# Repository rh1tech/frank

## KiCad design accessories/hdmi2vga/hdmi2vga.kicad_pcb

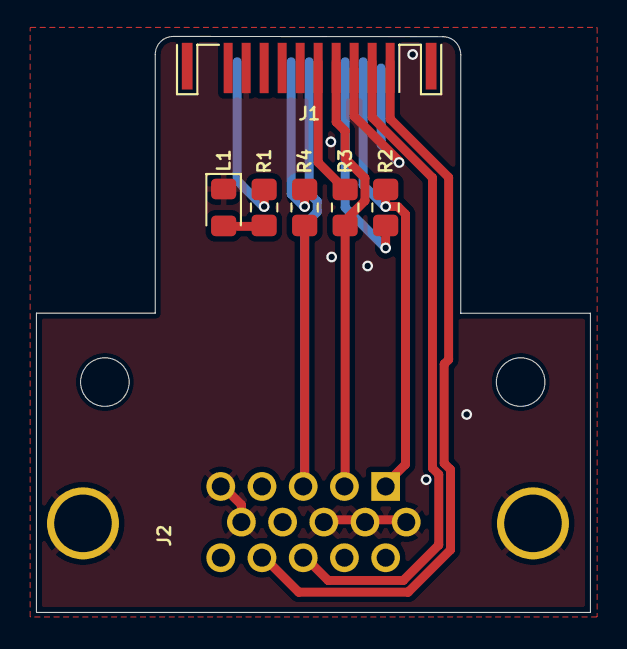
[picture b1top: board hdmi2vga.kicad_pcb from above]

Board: 2 copper layers, 30.8 x 32.0 mm, 9 parts (0 on the bottom side), 11 nets.

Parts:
H1, H2: MountingHole; Mounting Hole (2.7mm)
J1: HDMI; HDMI (male)
J2: VGA; D-SUB (15 pin, female)
L1: HDMI LED; LED (0805)
R1: 1K; Resistor (0805)
R2, R3, R4: 820R; Resistor (0805)

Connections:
/CLKN_VGA_B: J1.12 (CLKN), R4.1
/CLKP_VGA_BH: J1.10 (CLKP), J2.3, R4.2
/D0N_VGA_G: J1.9 (D0N), R3.1
/D0P_VGA_GH: J1.7 (D0P), J2.2, R3.2
/D1N_VGA_R: J1.6 (D1N), R2.1
/D1P_VGA_RH: J1.4 (D1P), J2.1, R2.2
/D2N_VGA_HS: J1.3 (D2N), J2.13
/D2P_VGA_VS: J1.1 (D2P), J2.14
GND: J1.2 (G_D2), J1.5 (G_D1), J1.8 (G_D0), J1.11 (G_CLK), J1.17 (G_DDC/CEC), J2.0, J2.5, J2.6, J2.7, J2.8, J2.10, L1.1 (K)
unnamed: J1.18 (+5V), R1.1
unnamed: L1.2 (A), R1.2

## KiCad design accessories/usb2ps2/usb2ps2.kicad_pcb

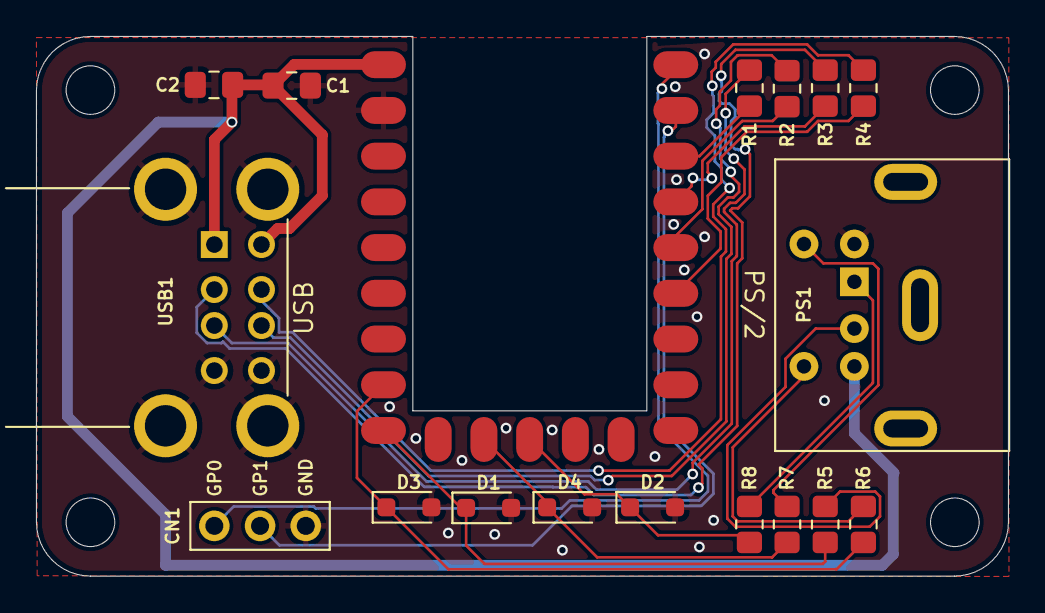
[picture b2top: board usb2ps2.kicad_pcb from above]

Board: 2 copper layers, 54.0 x 30.0 mm, 22 parts (0 on the bottom side), 20 nets.

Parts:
C1, C2: 10u; Capacitor (0805)
CN1: UART; Pin Header (1x03)
D1, D2, D3, D4: 3V3; Diode (SOD-323)
H1, H2, H3, H4: MountingHole; Mounting Hole (2.7mm)
PS1: PS/2; MiniDIN (6 Pin, female)
R1, R2, R3, R4: 22R; Resistor (0805)
R5, R6, R7, R8: 100R; Resistor (0805)
RP1: RP 2040 Zero; Raspberry Pi Zero (on board)
USB1: USB_A_Stacked; USB Type A (stacked)

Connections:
/GPIO0: CN1.1, RP1.1 (0)
/GPIO1: CN1.2, RP1.2 (1)
/GPIO2: R1.1, RP1.3 (2)
/GPIO3: R3.1, RP1.4 (3)
/GPIO4: R2.1, RP1.5 (4)
/GPIO5: R4.1, RP1.6 (5)
/GPIO11: D2.1 (K), R8.2, RP1.12 (11)
/GPIO12: D4.1 (K), R7.2, RP1.13 (12)
/GPIO14: D1.1 (K), R5.2, RP1.15 (14)
/GPIO15: D3.1 (K), R6.2, RP1.16 (15)
/PS2 with Diodes/KB_CLK: PS1.5, R7.1
/PS2 with Diodes/KB_DATA: PS1.1, R8.1
/PS2 with Diodes/MS_CLK: PS1.6, R6.1
/PS2 with Diodes/MS_DATA: PS1.2, R5.1
GND: C1.2, C2.2, CN1.3, D1.2 (A), D2.2 (A), D3.2 (A), D4.2 (A), PS1.3, RP1.22 (GND), USB1.4 (GND1), USB1.8 (GND2), USB1.9 (Shield)
unnamed: R1.2, USB1.3 (D1+)
unnamed: R3.2, USB1.2 (D1-)
unnamed: R2.2, USB1.7 (D2+)
unnamed: R4.2, USB1.6 (D2-)
VBUS: C1.1, C2.1, PS1.4, RP1.23 (5V), USB1.1 (VBUS1), USB1.5 (VBUS2)

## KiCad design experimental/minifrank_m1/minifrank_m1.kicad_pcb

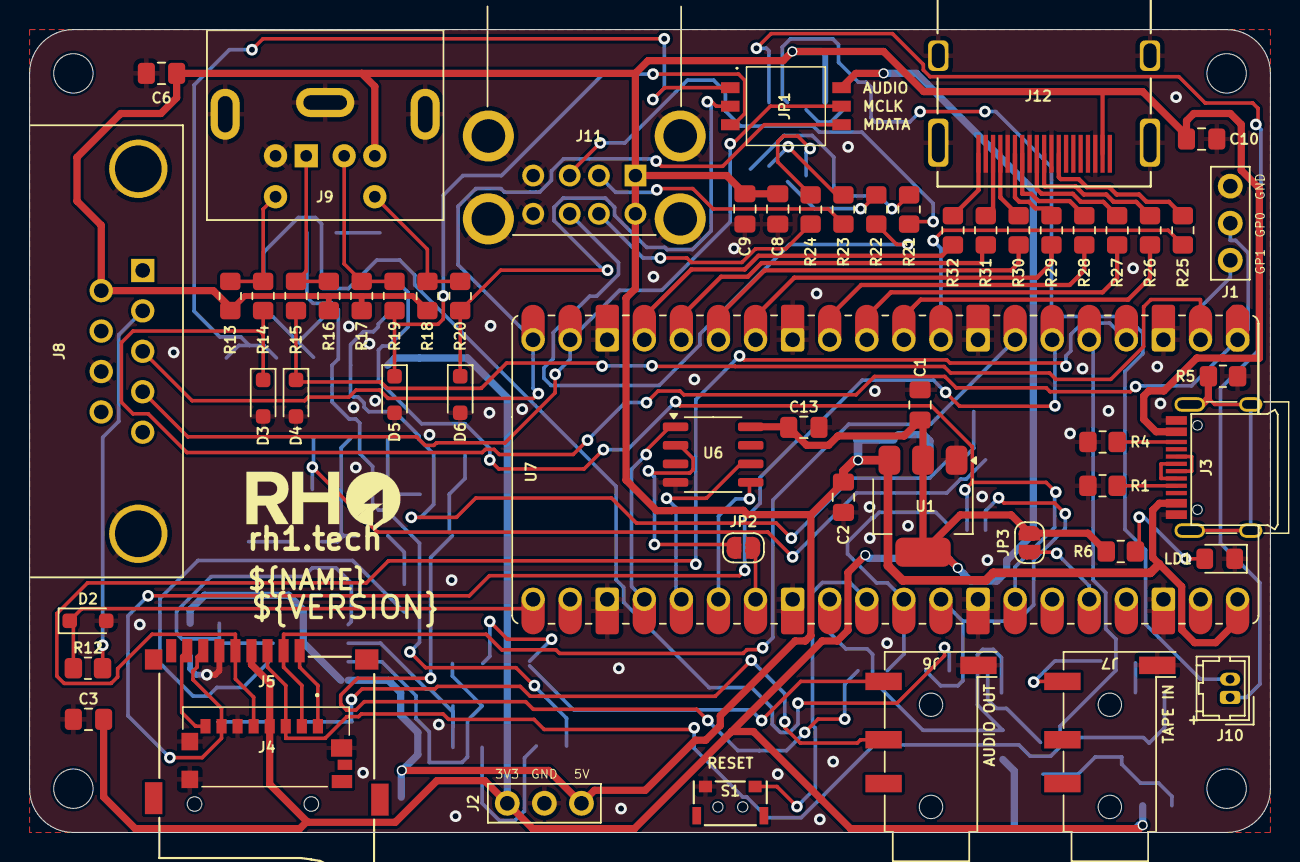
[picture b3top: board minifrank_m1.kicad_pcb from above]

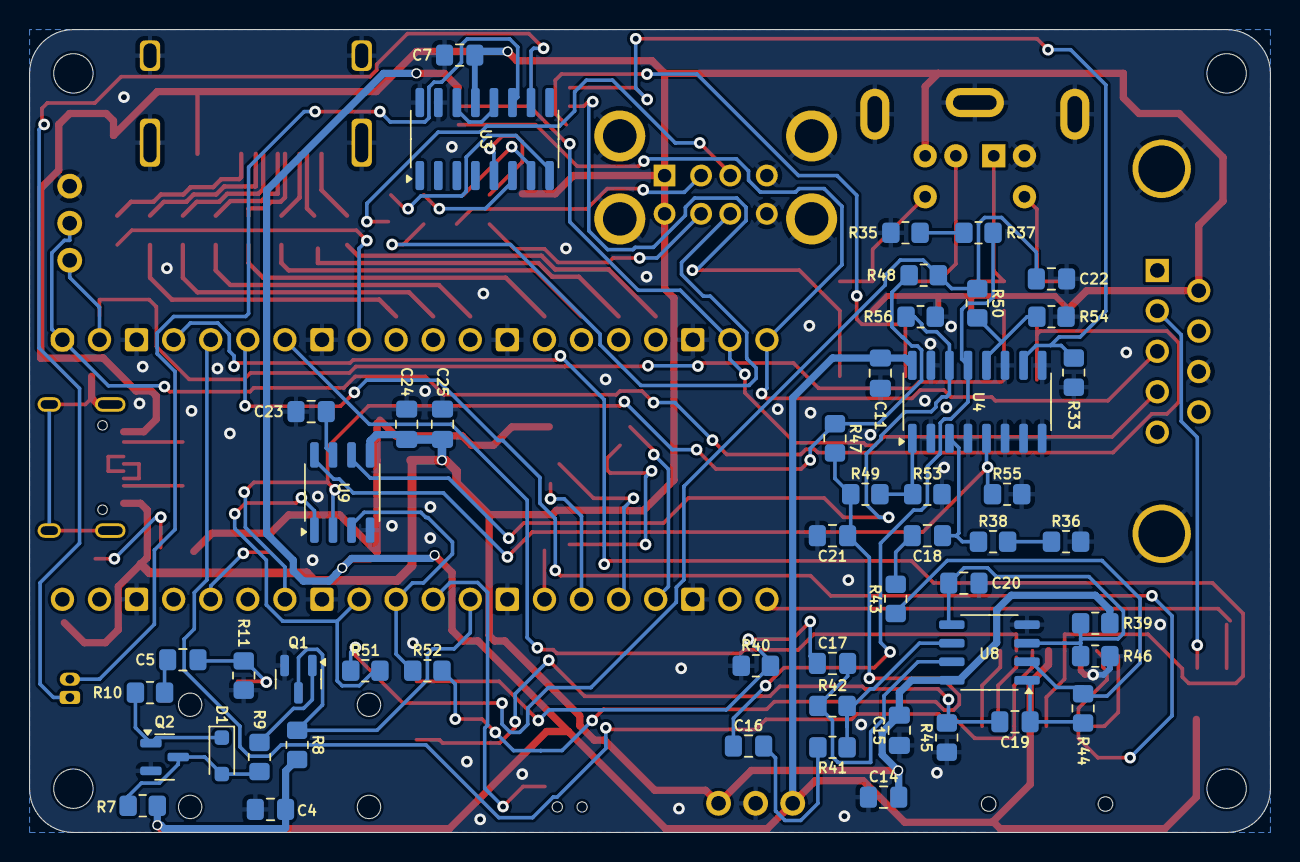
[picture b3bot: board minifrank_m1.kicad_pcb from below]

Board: 2 copper layers, 85.0 x 55.0 mm, 113 parts (51 on the bottom side), 91 nets.

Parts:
C1, C2, C8, C9, C14, C16, C17, C18, C19, C20, C23, C24: 10u; Capacitor (0805)
C3, C4, C5, C6, C10, C11, C13, C15, C25: 100n; Capacitor (0805)
C7: 4.7u; Capacitor (0805)
C21, C22: 47n; Capacitor (0805)
D1: 1N4148; Diode (SOD-323)
D2, D3, D4, D5, D6: 3V3; Diode (SOD-323)
H1, H2, H3, H4: MountingHole; Mounting Hole (2.7mm)
J1: UART; Pin Header (1x03)
J2: PWR; Pin Header (1x03)
J3: USB4215-03-A; USB Type C
J4: 0475710001; MicroSD (SMD, short)
J5: 104031-0811; MicroSD (SMD, long)
J6, J7: PJ-320D; Jack (3.5mm, PJ-320D)
J8: D-SUB 9 Male; D-SUB (9 pin, male, top mount)
J9: MDC-036; MiniDIN (6 Pin, female)
J10: USB HUB Data; Connector Female 1.25 JST 2P
J11: SS-52100-004; USB Type A (stacked)
J12: DC3RX19JA2; HDMI (female)
JP1: Main Jumpers; DS05127203BKSMTTR
JP2, JP3: Jumper (Solder); Jumper (solder)
LD1: Power; LED (0805)
Q1, Q2: BC850; SOT-23
R1, R4: 5.1K; Resistor (0805)
R5: 1M; Resistor (0805)
R6, R8, R12, R13, R16, R17, R18, R51, R52: 1K; Resistor (0805)
R7, R9, R10, R33, R37, R38, R39, R41, R43, R46, R49, R50: 10K; Resistor (0805)
R11, R14, R15, R19, R20: 100R; Resistor (0805)
R21, R22, R23, R24: 22R; Resistor (0805)
R25, R26, R27, R28, R29, R30, R31, R32: 270R; Resistor (0805)
R35, R36, R47, R48, R53, R54: 2K; Resistor (0805)
R40, R45: 20K; Resistor (0805)
R42, R44: 47K; Resistor (0805)
R55, R56: 470R; Resistor (0805)
S1: Reset; TACT-SIDE-4623
U1: NCP1117 3.3; SOT-223
U3: MW7211A; SOP-16
U4: 74HC4052D; SOP-16
U6: ESP-PSRAM32; SO-8
U7: Rasberry Pi Pico; Raspberry Pi Pico
U8: LM358; SO-8
U9: TDA1387T; SO-8

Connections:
+3V3: C1.1, C3.2, C4.1, C11.2, C13.1, J2.1, J4.P4 (VDD), J5.4 (VDD), JP1.6, JP3.2 (B), R6.2, R7.1, R8.1, U1.2 (VO), U4.16 (VCC), U6.8 (VCC)
/AMP_IN_L: C16.1, R37.1, U4.13 (1Z)
/AMP_IN_R: C18.1, R38.1, U4.3 (2Z)
/AUDIOSW: JP1.1, R33.2, U4.10 (S0)
/Audio Out/AMP_OUTL: C17.2, J6.T, R40.2
/Audio Out/AMP_OUTR: C19.2, J6.R, R45.2
/GPIO0: D3.1 (K), J1.2, R14.2, U7.1 (GPIO0)
/GPIO1: D4.1 (K), J1.3, R15.2, U7.2 (GPIO1)
/GPIO2: J4.P5 (CLK), J5.5 (CLK), U7.4 (GPIO2)
/GPIO3: J4.P3 (CMD), J5.3 (CMD), U7.5 (GPIO3)
/GPIO4: J4.P7 (DAT0), J5.7 (DAT0), U7.6 (GPIO4)
/GPIO5: J4.P2 (CD/DAT3), J5.2 (DAT3/CD), U7.7 (GPIO5)
/GPIO6: R25.2, U7.9 (GPIO6)
/GPIO7: R26.2, U7.10 (GPIO7)
/GPIO8: R27.2, U7.11 (GPIO8)
/GPIO9: R28.2, U7.12 (GPIO9)
/GPIO10: R29.2, U7.14 (GPIO10)
/GPIO11: R30.2, U7.15 (GPIO11)
/GPIO12: R31.2, U7.16 (GPIO12)
/GPIO13: R32.2, U7.17 (GPIO13)
/GPIO14: J8.4, JP1.5, U7.19 (GPIO14)
/GPIO15: J8.3, JP1.4, U7.20 (GPIO15)
/GPIO16: D2.1 (K), R12.1, U7.21 (GPIO16)
/GPIO18: U6.1 (~CE), U7.24 (GPIO18)
/GPIO19: U6.6 (SCLK), U7.25 (GPIO19)
/GPIO20: U6.5 (SI/SIO), U7.26 (GPIO20)
/GPIO21: JP2.2 (B), U7.27 (GPIO21)
/GPIO22: Q1.3 (C), R8.2, U7.29 (GPIO22)
/GPIO26: R52.2, U7.31 (GPIO26_ADC0), U9.3 (DATA)
/GPIO27: R51.2, U7.32 (GPIO27_ADC1), U9.1 (SCLK)
/GPIO28: R47.1, R48.1, U7.34 (GPIO28_ADC2), U9.2 (LRCK)
/KB_CLK: J9.5, R13.2, R14.1
/KB_DATA: J9.1, R15.1, R16.2
/MS_CLK: J9.6, R18.2, R20.1
/MS_CLK_3V: D6.1 (K), JP1.2, R20.2
/MS_DATA: J9.2, R17.2, R19.1
/MS_DATA_3V: D5.1 (K), JP1.3, R19.2
/PWM_OUT_L: R50.2, R54.1, U4.12 (1Y0)
/PWM_OUT_R: R49.2, R53.1, U4.1 (2Y0)
/Power/D+: J3.6 (DP1), J3.8 (DP2)
/Power/D-: J3.5 (DN2), J3.7 (DN1)
/RUN: S1.1, U7.30 (RUN)
/SD Card/DAT1: J4.P8 (DAT1), J5.8 (DAT1)
/SD Card/DAT2: J4.P1 (DAT2), J5.1 (DAT2)
/TDA_L: R56.2, U4.14 (1Y1), U9.6 (A_LEFT)
/TDA_R: R55.1, U4.5 (2Y1), U9.8 (A_RIGHT)
/USB Hub/DM_IN: J10.2, U3.10 (DMU)
/USB Hub/DP_IN: J10.1, U3.11 (DPU)
/USB_D1+: R21.1, U3.8 (DP3)
/USB_D1-: R23.1, U3.7 (DM3)
/USB_D2+: R22.1, U3.6 (DP2)
/USB_D2-: R24.1, U3.5 (DM2)
GND: C1.2, C2.2, C3.1, C4.2, C6.2, C7.2, C8.2, C9.2, C10.2, C11.1, C13.2, C14.1, C15.1, C20.1, C21.2, C22.2, C23.2, C24.2, C25.2, D2.2 (A), D3.2 (A), D4.2 (A), D5.2 (A), D6.2 (A), J1.1, J2.2, J3.1 (GND), J3.12 (GND), J4.G1 (GND_1), J4.G2 (GND_2), J4.G3 (GND_3), J4.P6 (VSS), J5.6 (VSS), J6.S, J7.S, J8.8, J9.3, J11.4 (GND1), J11.8 (GND2), J11.9 (Shield), J12.2 (G_D2), J12.5 (G_D1), J12.8 (G_D0), J12.11 (G_CLK), J12.17 (G_DDC/CEC), J12.20 (SHIELD1), J12.21 (SHIELD2), J12.22 (SHIELD3), J12.23 (SHIELD4), LD1.1 (K), Q1.2 (E), Q2.2 (E), R1.1, R4.1, R5.2, R11.2, R33.1, R35.2, R36.2, R40.1, R45.1, R46.1, R53.2, R54.2, R55.2, R56.1, S1.2, U1.1 (GND), U3.15 (GND), U3.16 (GND), U4.2 (2Y2), U4.4 (2Y3), U4.6 (~E), U4.7 (VEE), U4.8 (GND), U4.9 (S1), U4.11 (1Y3), U4.15 (1Y2), U6.4 (VSS), U7.3 (GND), U7.8 (GND), U7.13 (GND), U7.18 (GND), U7.23 (GND), U7.28 (GND), U7.33 (AGND), U7.38 (GND), U8.4 (V-), U9.4 (AGND)
unnamed: C5.1, J7.T, R11.1
unnamed: C5.2, R10.1
unnamed: C16.2, R41.2
unnamed: C17.1, R42.1, U8.7
unnamed: C18.2, R43.2
unnamed: C19.1, R44.1, U8.1
unnamed: C21.1, R47.2, R49.1, R52.1
unnamed: C22.1, R48.2, R50.1, R51.1
unnamed: D1.2 (A), Q2.3 (C), R7.2, R9.1
unnamed: D1.1 (K), Q2.1 (B), R10.2
unnamed: J3.4 (CC1), R1.2
unnamed: J3.10 (CC2), R4.2
unnamed: J3.13 (SHIELD), R5.1
unnamed: J8.2, R12.2
unnamed: J11.3 (D1+), R21.2
unnamed: J11.2 (D1-), R23.2
unnamed: J11.7 (D2+), R22.2
unnamed: J11.6 (D2-), R24.2
unnamed: J12.12 (CLKN), R25.1
unnamed: J12.10 (CLKP), R26.1
unnamed: J12.9 (D0N), R27.1
unnamed: J12.7 (D0P), R28.1
unnamed: J12.6 (D1N), R29.1
unnamed: J12.4 (D1P), R30.1
unnamed: J12.3 (D2N), R31.1
unnamed: J12.1 (D2P), R32.1
unnamed: JP2.1 (A), U6.2 (SO/SIO)
unnamed: JP3.1 (A), U7.36 (3V3)
unnamed: LD1.2 (A), R6.1
unnamed: Q1.1 (B), R9.2
unnamed: R35.1, R37.2
unnamed: R36.1, R38.2
unnamed: U3.12 (VD33), U3.14 (VD3)
unnamed: C20.2, R39.1, R46.2, U8.3 (+), U8.5 (+)
unnamed: R43.1, R44.2, U8.2 (-)
unnamed: R41.1, R42.2, U8.6 (-)
unnamed: C23.1, U9.7 (FLT)
VBUS: C2.1, C6.1, C7.1, C8.1, C9.1, C10.1, C14.2, C15.2, C24.1, C25.1, J2.3, J3.2 (VBUS), J3.11 (VBUS), J8.6, J9.4, J11.1 (VBUS1), J11.5 (VBUS2), J12.18 (+5V), R13.1, R16.1, R17.1, R18.1, R39.2, U1.3 (VI), U3.13 (VDD5), U7.40 (VBUS), U8.8 (V+), U9.5 (VA)

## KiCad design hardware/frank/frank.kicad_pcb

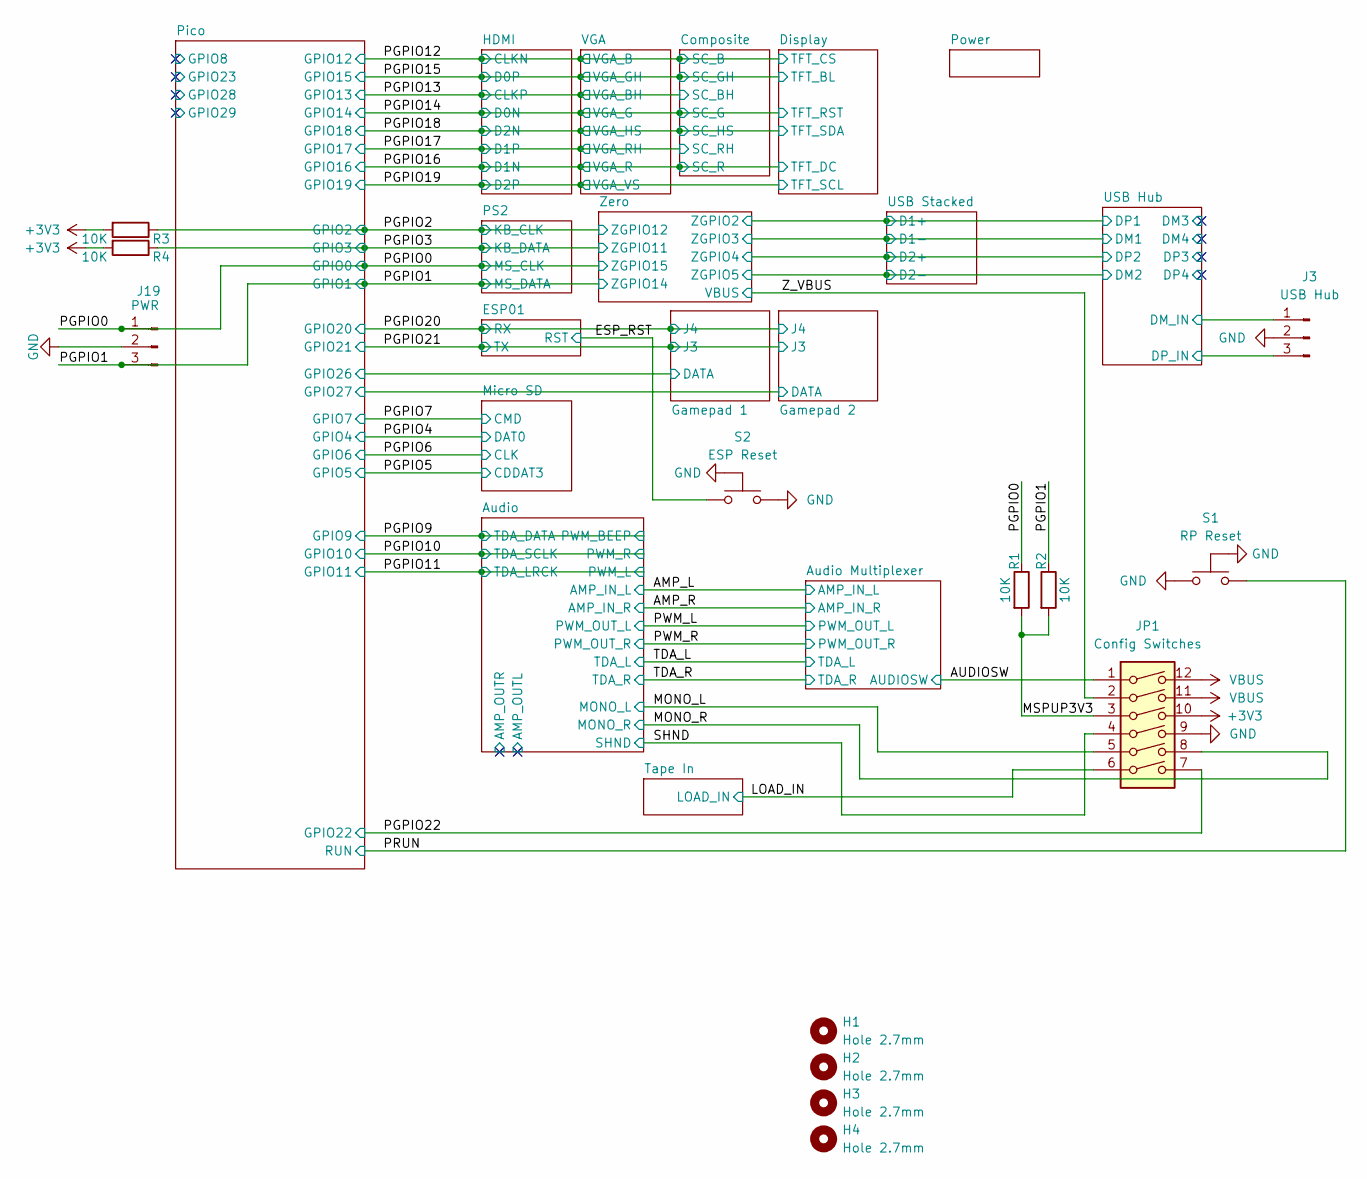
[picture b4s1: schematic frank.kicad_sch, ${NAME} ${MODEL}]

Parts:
H1, H2, H3, H4: Hole 2.7mm; MountingHole_2.7mm
J3: USB Hub; JST_SH_1x03_P1.00mm_Vertical
J19: PWR; JST_SH_1x03_P1.00mm_Vertical_UART
JP1: Config Switches; SOIC-12_P1.27mm
R1, R2, R3, R4: 10K; R_0805_2012Metric
S1: RP Reset; Button_SMD_TS1234VW
S2: ESP Reset; Button_SMD_TS1234VW

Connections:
+3V3: JP1.10, R3.2, R4.2; also elsewhere on the board
/AUDIOSW: JP1.1; also elsewhere on the board
/ESP_RST: S2.1; also elsewhere on the board
/LOAD_IN: JP1.6; also elsewhere on the board
/MONO_L: JP1.5; also elsewhere on the board
/MONO_R: JP1.8; also elsewhere on the board
/MSPUP3V3: JP1.3, R1.2, R2.2
/PGPIO0: J19.1, R1.1; also elsewhere on the board
/PGPIO1: J19.3, R2.1; also elsewhere on the board
/PGPIO2: R3.1; also elsewhere on the board
/PGPIO3: R4.1; also elsewhere on the board
/PGPIO22: JP1.7; also elsewhere on the board
/PRUN: S1.1; also elsewhere on the board
/SHND: JP1.4; also elsewhere on the board
/USB Hub/DM_IN: J3.1; also elsewhere on the board
/USB Hub/DP_IN: J3.3; also elsewhere on the board
/Z_VBUS: JP1.2; also elsewhere on the board
GND: J3.2, J19.2, JP1.9, S1.2, S1.3 (GND), S2.2, S2.3 (GND); also elsewhere on the board
VBUS: JP1.11, JP1.12; also elsewhere on the board

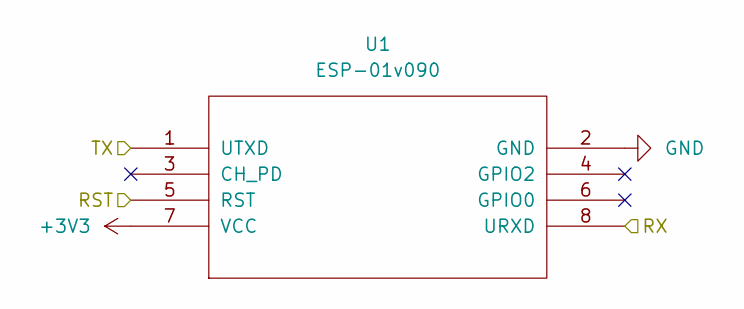
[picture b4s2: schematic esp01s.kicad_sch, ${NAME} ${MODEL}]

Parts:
U1: ESP-01v090; ESP-01

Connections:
+3V3: U1.7 (VCC); also elsewhere on the board
/ESP_RST: U1.5 (RST); also elsewhere on the board
/PGPIO20: U1.8 (URXD); also elsewhere on the board
/PGPIO21: U1.1 (UTXD); also elsewhere on the board
GND: U1.2 (GND); also elsewhere on the board

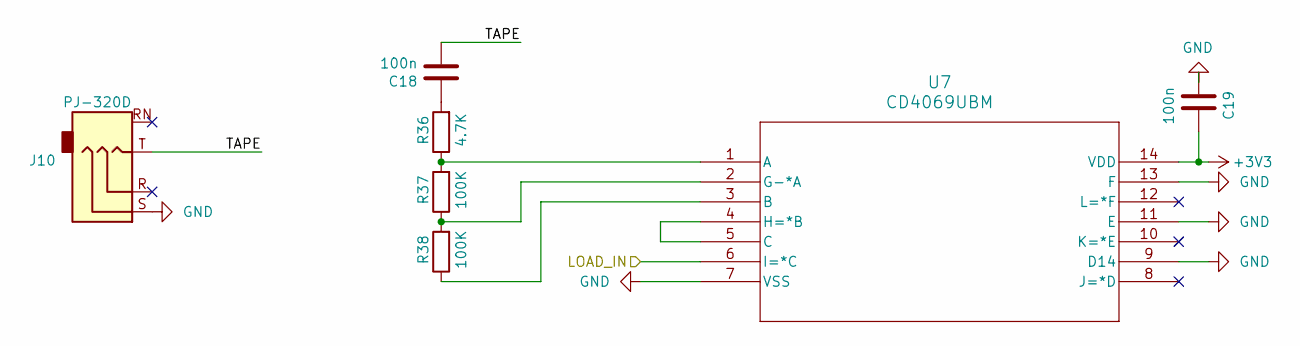
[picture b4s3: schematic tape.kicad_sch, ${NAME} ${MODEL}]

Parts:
C18, C19: 100n; C_0805_2012Metric
J10: PJ-320D; AudioJack_3.5mm_PJ320D
R36: 4.7K; R_0805_2012Metric
R37, R38: 100K; R_0805_2012Metric
U7: CD4069UBM; SOIC-14_P1.27mm

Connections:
+3V3: C19.1, U7.14 (VDD); also elsewhere on the board
/LOAD_IN: U7.6 (I=*C); also elsewhere on the board
/Tape In/TAPE: C18.2, J10.T
GND: C19.2, J10.S, U7.7 (VSS), U7.9 (D14), U7.11 (E), U7.13 (F); also elsewhere on the board
unnamed: C18.1, R36.2
unnamed: R36.1, R37.2, U7.1 (A)
unnamed: R38.1, U7.3 (B)
unnamed: U7.4 (H=*B), U7.5 (C)
unnamed: R37.1, R38.2, U7.2 (G-*A)

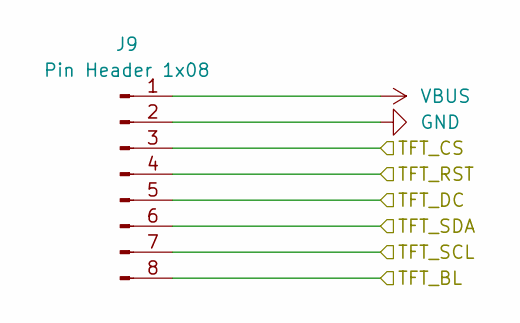
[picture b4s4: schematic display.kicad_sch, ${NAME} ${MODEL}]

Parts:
J9: Pin Header 1x08; JST_GH_1x08_P1.25mm

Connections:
/PGPIO12: J9.3; also elsewhere on the board
/PGPIO14: J9.4; also elsewhere on the board
/PGPIO15: J9.8; also elsewhere on the board
/PGPIO16: J9.5; also elsewhere on the board
/PGPIO18: J9.6; also elsewhere on the board
/PGPIO19: J9.7; also elsewhere on the board
GND: J9.2; also elsewhere on the board
VBUS: J9.1; also elsewhere on the board

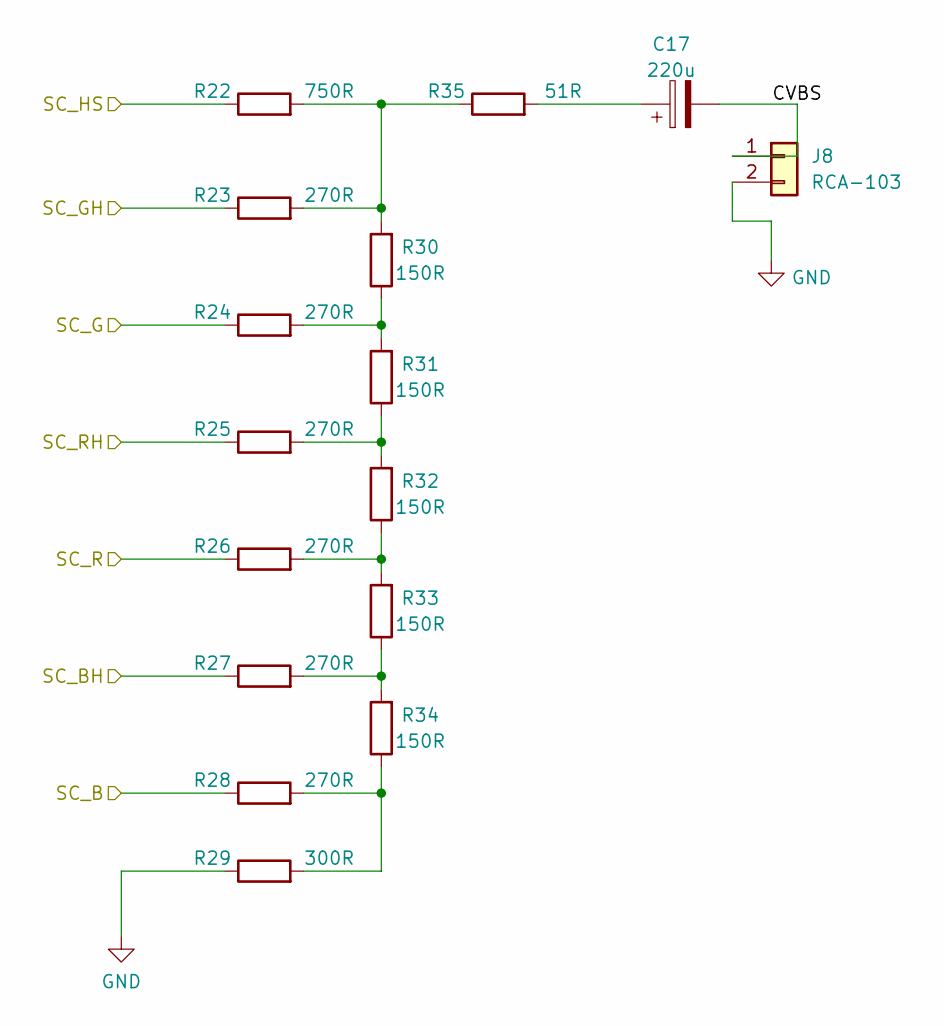
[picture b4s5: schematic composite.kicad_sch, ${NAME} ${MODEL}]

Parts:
C17: 220u; C_Radial_D6.3mm_P2.50mm
J8: RCA-103; BarrelJack_RCJ-012
R22: 750R; R_0805_2012Metric
R23, R24, R25, R26, R27, R28: 270R; R_0805_2012Metric
R29: 300R; R_0805_2012Metric
R30, R31, R32, R33, R34: 150R; R_0805_2012Metric
R35: 51R; R_0805_2012Metric

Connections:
/Composite/CVBS: C17.2, J8.1
/PGPIO12: R28.1; also elsewhere on the board
/PGPIO13: R27.1; also elsewhere on the board
/PGPIO14: R24.1; also elsewhere on the board
/PGPIO15: R23.1; also elsewhere on the board
/PGPIO16: R26.1; also elsewhere on the board
/PGPIO17: R25.1; also elsewhere on the board
/PGPIO18: R22.1; also elsewhere on the board
GND: J8.2, R29.1; also elsewhere on the board
unnamed: C17.1, R35.2
unnamed: R22.2, R23.2, R30.2, R35.1
unnamed: R24.2, R30.1, R31.2
unnamed: R25.2, R31.1, R32.2
unnamed: R26.2, R32.1, R33.2
unnamed: R27.2, R33.1, R34.2
unnamed: R28.2, R29.2, R34.1

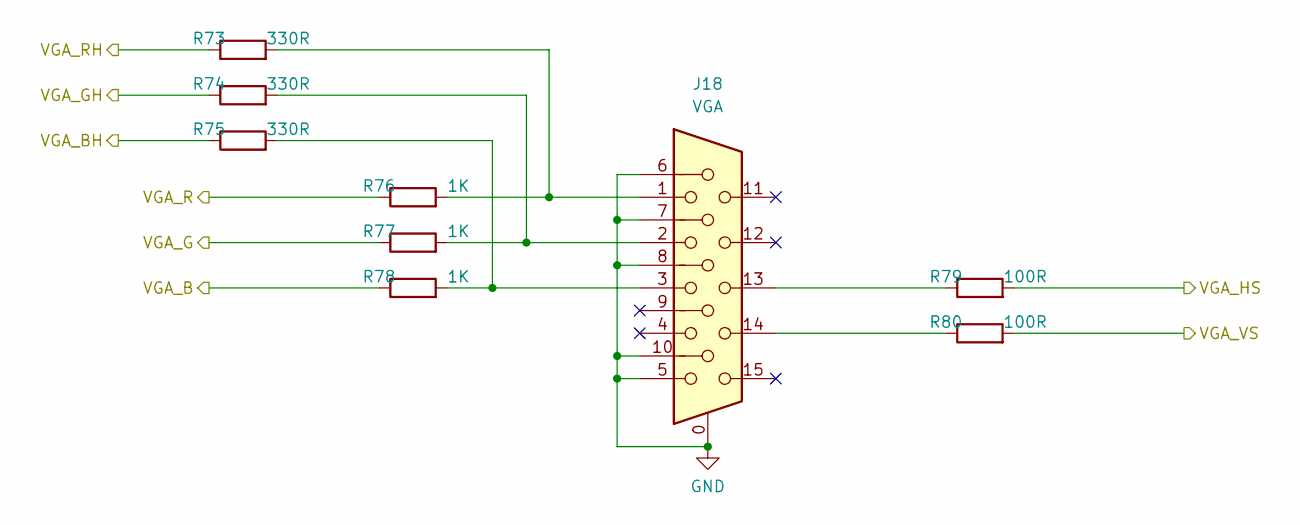
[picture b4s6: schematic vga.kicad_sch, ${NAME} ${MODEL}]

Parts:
J18: VGA; DSUB-15_Female
R73, R74, R75: 330R; R_0805_2012Metric
R76, R77, R78: 1K; R_0805_2012Metric
R79, R80: 100R; R_0805_2012Metric

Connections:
/PGPIO12: R78.1; also elsewhere on the board
/PGPIO13: R75.1; also elsewhere on the board
/PGPIO14: R77.1; also elsewhere on the board
/PGPIO15: R74.1; also elsewhere on the board
/PGPIO16: R76.1; also elsewhere on the board
/PGPIO17: R73.1; also elsewhere on the board
/PGPIO18: R79.2; also elsewhere on the board
/PGPIO19: R80.2; also elsewhere on the board
GND: J18.0, J18.5, J18.6, J18.7, J18.8, J18.10; also elsewhere on the board
unnamed: J18.1, R73.2, R76.2
unnamed: J18.2, R74.2, R77.2
unnamed: J18.3, R75.2, R78.2
unnamed: J18.13, R79.1
unnamed: J18.14, R80.1

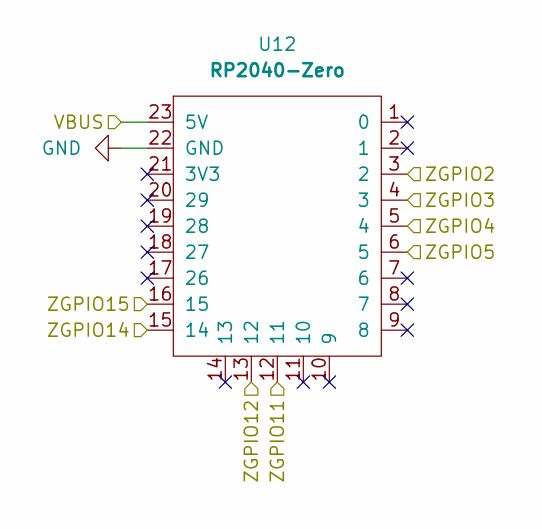
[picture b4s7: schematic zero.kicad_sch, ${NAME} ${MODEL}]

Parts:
U12: RP2040-Zero; RaspberryPi_Zero

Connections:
/PGPIO0: U12.16 (15); also elsewhere on the board
/PGPIO1: U12.15 (14); also elsewhere on the board
/PGPIO2: U12.13 (12); also elsewhere on the board
/PGPIO3: U12.12 (11); also elsewhere on the board
/USB Hub/DM1: U12.4 (3); also elsewhere on the board
/USB Hub/DM2: U12.6 (5); also elsewhere on the board
/USB Hub/DP1: U12.3 (2); also elsewhere on the board
/USB Hub/DP2: U12.5 (4); also elsewhere on the board
/Z_VBUS: U12.23 (5V); also elsewhere on the board
GND: U12.22 (GND); also elsewhere on the board

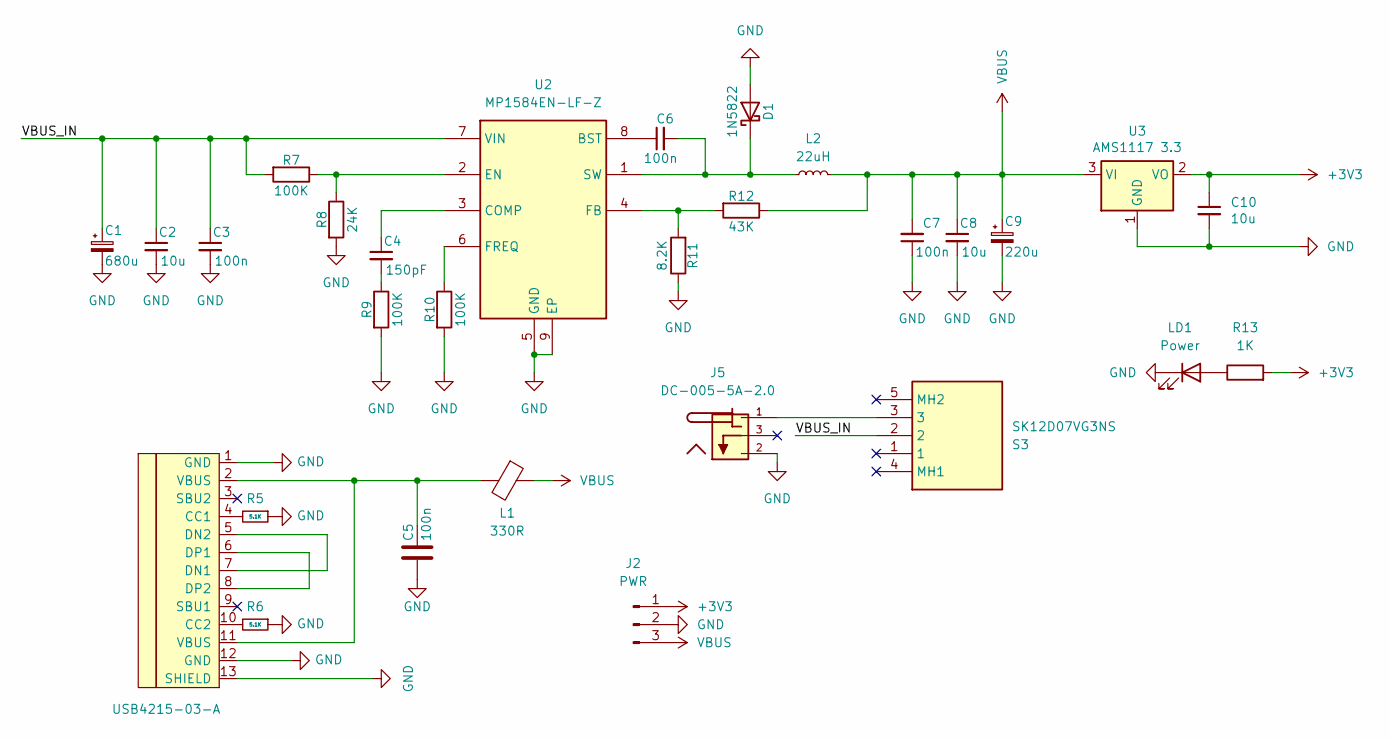
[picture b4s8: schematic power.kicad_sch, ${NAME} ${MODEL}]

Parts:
C1: 680u; C_Radial_D8.0mm_P3.50mm
C2, C8, C10: 10u; C_0805_2012Metric
C3, C5, C6, C7: 100n; C_0805_2012Metric
C4: 150pF; R_0805_2012Metric
C9: 220u; C_Radial_D6.3mm_P2.50mm
D1: 1N5822; D_SMA
J2: PWR; PinHeader_1x03_P2.54mm
J4: USB4215-03-A; USB_C_Receptacle; LCSC C165948
J5: DC-005-5A-2.0; BarrelJack_DC-005; PARTREV A0
L1: 330R; R_0805_2012Metric
L2: 22uH; Inductor_CDRH104RNP
LD1: Power; LED_0805
R5, R6: 5.1K; R_0805_2012Metric
R7, R9, R10: 100K; R_0805_2012Metric
R8: 24K; R_0805_2012Metric
R11: 8.2K; R_0805_2012Metric
R12: 43K; R_0805_2012Metric
R13: 1K; R_0805_2012Metric
S3: SK12D07VG3NS; Switch_Slide_SK12D07VG3NS; Mouser Part Number 611-SK12D07VG3NS
U2: MP1584EN-LF-Z; SOIC-9_P1.27mm; Mouser Part Number 946-MP1584ENLFZ
U3: AMS1117 3.3; SOT-223

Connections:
+3V3: C10.1, J2.1, R13.2, U3.2 (VO); also elsewhere on the board
/Power/VBUS_IN: C1.1, C2.1, C3.1, R7.2, S3.2, U2.7 (VIN)
GND: C1.2, C2.2, C3.2, C5.2, C7.1, C8.2, C9.2, C10.2, D1.2 (A), J2.2, J4.1 (GND), J4.12 (GND), J4.13 (SHIELD), J5.2, LD1.1 (K), R5.1, R6.1, R8.2, R9.2, R10.2, R11.1, U2.5 (GND), U2.9 (EP), U3.1 (GND); also elsewhere on the board
unnamed: C4.2, R9.1
unnamed: C5.1, J4.2 (VBUS), J4.11 (VBUS), L1.2
unnamed: C6.2, D1.1 (K), L2.1, U2.1 (SW)
unnamed: J4.4 (CC1), R5.2
unnamed: J4.10 (CC2), R6.2
unnamed: J4.5 (DN2), J4.7 (DN1)
unnamed: J4.6 (DP1), J4.8 (DP2)
unnamed: J5.1, S3.3
unnamed: LD1.2 (A), R13.1
unnamed: C6.1, U2.8 (BST)
unnamed: C4.1, U2.3 (COMP)
unnamed: R7.1, R8.1, U2.2 (EN)
unnamed: R11.2, R12.2, U2.4 (FB)
unnamed: R10.1, U2.6 (FREQ)
VBUS: C7.2, C8.1, C9.1, J2.3, L1.1, L2.2, R12.1, U3.3 (VI); also elsewhere on the board

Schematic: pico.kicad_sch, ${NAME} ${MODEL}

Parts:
JP2: 3V3 Jumper; Jumper_Solder
U6: Rasberry Pi Pico 1/2; RaspberryPi_Pico

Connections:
+3V3: JP2.2 (B); also elsewhere on the board
/Gamepad 1/DATA: U6.31 (GPIO26_ADC0); also elsewhere on the board
/Gamepad 2/DATA: U6.32 (GPIO27_ADC1); also elsewhere on the board
/PGPIO0: U6.1 (GPIO0); also elsewhere on the board
/PGPIO1: U6.2 (GPIO1); also elsewhere on the board
/PGPIO2: U6.4 (GPIO2); also elsewhere on the board
/PGPIO3: U6.5 (GPIO3); also elsewhere on the board
/PGPIO4: U6.6 (GPIO4); also elsewhere on the board
/PGPIO5: U6.7 (GPIO5); also elsewhere on the board
/PGPIO6: U6.9 (GPIO6); also elsewhere on the board
/PGPIO7: U6.10 (GPIO7); also elsewhere on the board
/PGPIO9: U6.12 (GPIO9); also elsewhere on the board
/PGPIO10: U6.14 (GPIO10); also elsewhere on the board
/PGPIO11: U6.15 (GPIO11); also elsewhere on the board
/PGPIO12: U6.16 (GPIO12); also elsewhere on the board
/PGPIO13: U6.17 (GPIO13); also elsewhere on the board
/PGPIO14: U6.19 (GPIO14); also elsewhere on the board
/PGPIO15: U6.20 (GPIO15); also elsewhere on the board
/PGPIO16: U6.21 (GPIO16); also elsewhere on the board
/PGPIO17: U6.22 (GPIO17); also elsewhere on the board
/PGPIO18: U6.24 (GPIO18); also elsewhere on the board
/PGPIO19: U6.25 (GPIO19); also elsewhere on the board
/PGPIO20: U6.26 (GPIO20); also elsewhere on the board
/PGPIO21: U6.27 (GPIO21); also elsewhere on the board
/PGPIO22: U6.29 (GPIO22); also elsewhere on the board
/PRUN: U6.30 (RUN); also elsewhere on the board
/Pico/GPIO8: U6.11 (GPIO8)
/Pico/GPIO8_1: U6.11 (GPIO8)
/Pico/GPIO23: U6.37 (3V3_EN)
/Pico/GPIO23_1: U6.37 (3V3_EN)
/Pico/GPIO28: U6.34 (GPIO28_ADC2)
/Pico/GPIO28_1: U6.34 (GPIO28_ADC2)
/Pico/GPIO29: U6.35 (ADC_VREF)
/Pico/GPIO29_1: U6.35 (ADC_VREF)
GND: U6.3 (GND), U6.8 (GND), U6.13 (GND), U6.18 (GND), U6.23 (GND), U6.28 (GND), U6.33 (AGND), U6.38 (GND); also elsewhere on the board
unnamed: JP2.1 (A), U6.36 (3V3)
VBUS: U6.40 (VBUS); also elsewhere on the board

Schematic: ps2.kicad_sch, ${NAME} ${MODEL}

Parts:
C11, C12, C13, C14: 100n; C_0805_2012Metric
J6: MDC-036; MiniDIN_6pin_Female
U4: TXS0104EDR; SOIC-14_P1.27mm; Mouser Part Number 595-TXS0104EDR

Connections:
+3V3: C12.1, C13.1, U4.1 (VCCA), U4.8 (OE); also elsewhere on the board
/PGPIO0: U4.4 (A3); also elsewhere on the board
/PGPIO1: U4.5 (A4); also elsewhere on the board
/PGPIO2: U4.2 (A1); also elsewhere on the board
/PGPIO3: U4.3 (A2); also elsewhere on the board
/PS2/KB_CLK_5V: J6.5, U4.13 (B1)
/PS2/KB_DATA_5V: J6.1, U4.12 (B2)
/PS2/MS_CLK_5V: J6.6, U4.11 (B3)
/PS2/MS_DATA_5V: J6.2, U4.10 (B4)
GND: C11.2, C12.2, C13.2, C14.2, J6.3, U4.7 (GND); also elsewhere on the board
VBUS: C11.1, C14.1, J6.4, U4.14 (VCCB); also elsewhere on the board

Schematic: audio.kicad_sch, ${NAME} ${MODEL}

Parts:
J11: PAM L; JST_GH_1x02_P1.25mm
J12: PAM R; JST_GH_1x02_P1.25mm
J13: PJ-320D; AudioJack_3.5mm_PJ320D

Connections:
/Audio/AMP_OUTL: J13.T; also elsewhere on the board
/Audio/AMP_OUTR: J13.R; also elsewhere on the board
/Audio/AMP_PAM_OUTL_M: J11.2; also elsewhere on the board
/Audio/AMP_PAM_OUTL_P: J11.1; also elsewhere on the board
/Audio/AMP_PAM_OUTR_M: J12.2; also elsewhere on the board
/Audio/AMP_PAM_OUTR_P: J12.1; also elsewhere on the board
GND: J13.S; also elsewhere on the board

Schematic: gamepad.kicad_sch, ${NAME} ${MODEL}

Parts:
D3: 3V3; D_miniMELF
J14: GP2; DSUB-9_Male_TopMount
R67: 1K; R_0805_2012Metric

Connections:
/Gamepad 1/DATA: D3.1 (K), R67.1; also elsewhere on the board
/PGPIO20: J14.4; also elsewhere on the board
/PGPIO21: J14.3; also elsewhere on the board
GND: D3.2 (A), J14.8; also elsewhere on the board
unnamed: J14.2, R67.2
VBUS: J14.6; also elsewhere on the board

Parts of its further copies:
D4: 3V3; D_miniMELF
J15: GP2; DSUB-9_Male_TopMount
R68: 1K; R_0805_2012Metric

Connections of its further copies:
/Gamepad 2/DATA: D4.1 (K), R68.1; also elsewhere on the board
/PGPIO20: J15.4; also elsewhere on the board
/PGPIO21: J15.3; also elsewhere on the board
GND: D4.2 (A), J15.8; also elsewhere on the board
unnamed: J15.2, R68.2
VBUS: J15.6; also elsewhere on the board

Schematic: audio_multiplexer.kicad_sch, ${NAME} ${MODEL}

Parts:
C37: 100n; C_0805_2012Metric
R66: 10K; R_0805_2012Metric
U11: 74HC4052D; SOP-16_P1.27mm; Mouser Part Number 771-74HC4052D-T

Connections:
/AMP_L: U11.13 (1Z); also elsewhere on the board
/AMP_R: U11.3 (2Z); also elsewhere on the board
/AUDIOSW: R66.2, U11.10 (S0); also elsewhere on the board
/PWM_L: U11.12 (1Y0); also elsewhere on the board
/PWM_R: U11.1 (2Y0); also elsewhere on the board
/TDA_L: U11.14 (1Y1); also elsewhere on the board
/TDA_R: U11.5 (2Y1); also elsewhere on the board
GND: C37.1, R66.1, U11.2 (2Y2), U11.4 (2Y3), U11.6 (~E), U11.7 (VEE), U11.8 (GND), U11.9 (S1), U11.11 (1Y3), U11.15 (1Y2); also elsewhere on the board
VBUS: C37.2, U11.16 (VCC); also elsewhere on the board

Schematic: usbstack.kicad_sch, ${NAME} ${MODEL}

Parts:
C39, C40: 10u; C_0805_2012Metric
J17: SS-52100-004; USB_A_Stacked
R69, R70, R71, R72: 22R; R_0805_2012Metric

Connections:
/USB Hub/DM1: R70.1; also elsewhere on the board
/USB Hub/DM2: R72.1; also elsewhere on the board
/USB Hub/DP1: R69.1; also elsewhere on the board
/USB Hub/DP2: R71.1; also elsewhere on the board
GND: C39.2, C40.2, J17.4 (GND1), J17.8 (GND2), J17.SH (Shield); also elsewhere on the board
unnamed: J17.3 (D1+), R69.2
unnamed: J17.2 (D1-), R70.2
unnamed: J17.7 (D2+), R71.2
unnamed: J17.6 (D2-), R72.2
VBUS: C39.1, C40.1, J17.1 (VBUS1), J17.5 (VBUS2); also elsewhere on the board

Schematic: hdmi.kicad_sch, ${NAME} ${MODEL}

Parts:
C16: 100n; C_0805_2012Metric
D2: 1N5819WS; D_SOD-323
J7: HDMI-001 19PCBTP; HDMI_Female; LCSC C138388
R14, R15, R16, R17, R18, R19, R20, R21: 270R; R_0805_2012Metric

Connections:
/PGPIO12: R16.2; also elsewhere on the board
/PGPIO13: R20.2; also elsewhere on the board
/PGPIO14: R14.2; also elsewhere on the board
/PGPIO15: R17.2; also elsewhere on the board
/PGPIO16: R18.2; also elsewhere on the board
/PGPIO17: R21.2; also elsewhere on the board
/PGPIO18: R15.2; also elsewhere on the board
/PGPIO19: R19.2; also elsewhere on the board
GND: C16.2, J7.2 (G_D2), J7.5 (G_D1), J7.8 (G_D0), J7.11 (G_CLK), J7.17 (G_DDC/CEC), J7.20 (SHIELD1), J7.21 (SHIELD2), J7.22 (SHIELD3), J7.23 (SHIELD4); also elsewhere on the board
unnamed: C16.1, D2.1 (K), J7.18 (+5V)
unnamed: J7.12 (CLKN), R16.1
unnamed: J7.10 (CLKP), R20.1
unnamed: J7.9 (D0N), R14.1
unnamed: J7.7 (D0P), R17.1
unnamed: J7.6 (D1N), R18.1
unnamed: J7.4 (D1P), R21.1
unnamed: J7.3 (D2N), R15.1
unnamed: J7.1 (D2P), R19.1
VBUS: D2.2 (A); also elsewhere on the board

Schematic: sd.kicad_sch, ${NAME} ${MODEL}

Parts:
C38: 100n; C_0805_2012Metric
J16: 104031-0811; MicroSD_SMD_Long

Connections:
+3V3: C38.2, J16.4 (VDD); also elsewhere on the board
/PGPIO4: J16.7 (DAT0); also elsewhere on the board
/PGPIO5: J16.2 (DAT3/CD); also elsewhere on the board
/PGPIO6: J16.5 (CLK); also elsewhere on the board
/PGPIO7: J16.3 (CMD); also elsewhere on the board
GND: C38.1, J16.6 (VSS), J16.SH (SHIELD); also elsewhere on the board

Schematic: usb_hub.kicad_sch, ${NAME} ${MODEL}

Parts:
C15: 4.7u; C_0805_2012Metric; LCSC C1746
U5: MW7211A; SOP-16_P1.27mm

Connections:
/USB Hub/DM1: U5.7 (DM3); also elsewhere on the board
/USB Hub/DM2: U5.5 (DM2); also elsewhere on the board
/USB Hub/DM3: U5.3 (DM1)
/USB Hub/DM4: U5.1 (DM0)
/USB Hub/DM_IN: U5.10 (DMU); also elsewhere on the board
/USB Hub/DP1: U5.8 (DP3); also elsewhere on the board
/USB Hub/DP2: U5.6 (DP2); also elsewhere on the board
/USB Hub/DP3: U5.4 (DP1)
/USB Hub/DP4: U5.2 (DP0)
/USB Hub/DP_IN: U5.11 (DPU); also elsewhere on the board
GND: C15.2, U5.15 (GND), U5.16 (GND); also elsewhere on the board
unnamed: U5.12 (VD33), U5.14 (VD3)
VBUS: C15.1, U5.13 (VDD5); also elsewhere on the board

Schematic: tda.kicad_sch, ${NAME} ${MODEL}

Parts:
C22, C24: 10u; C_0805_2012Metric
C23: 100n; C_0805_2012Metric
R47: 100R; R_0805_2012Metric
R48, R49: 470R; R_0805_2012Metric
U8: TDA1387T; SO-8

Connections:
/PGPIO9: U8.3 (DATA); also elsewhere on the board
/PGPIO10: U8.1 (SCLK); also elsewhere on the board
/PGPIO11: U8.2 (LRCK); also elsewhere on the board
/TDA_L: R49.2, U8.6 (A_LEFT); also elsewhere on the board
/TDA_R: R48.1, U8.8 (A_RIGHT); also elsewhere on the board
GND: C22.2, C23.2, C24.2, R48.2, R49.1, U8.4 (AGND); also elsewhere on the board
unnamed: C24.1, U8.7 (FLT)
unnamed: C22.1, C23.1, R47.1, U8.5 (VA)
VBUS: R47.2; also elsewhere on the board
